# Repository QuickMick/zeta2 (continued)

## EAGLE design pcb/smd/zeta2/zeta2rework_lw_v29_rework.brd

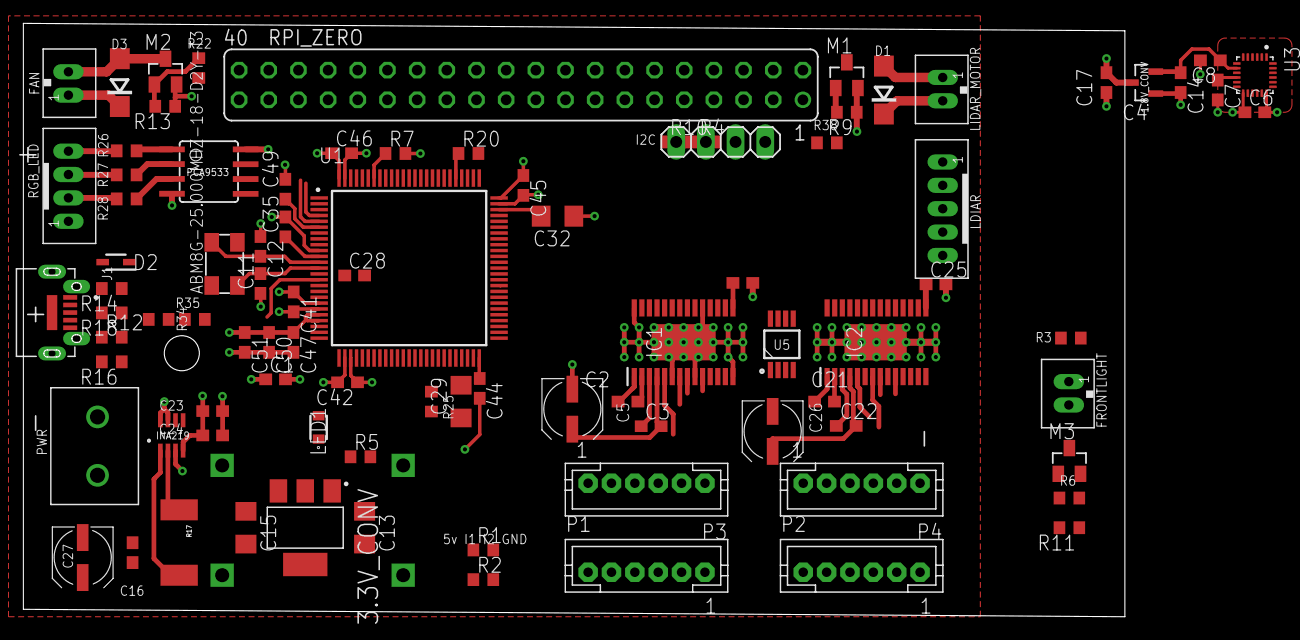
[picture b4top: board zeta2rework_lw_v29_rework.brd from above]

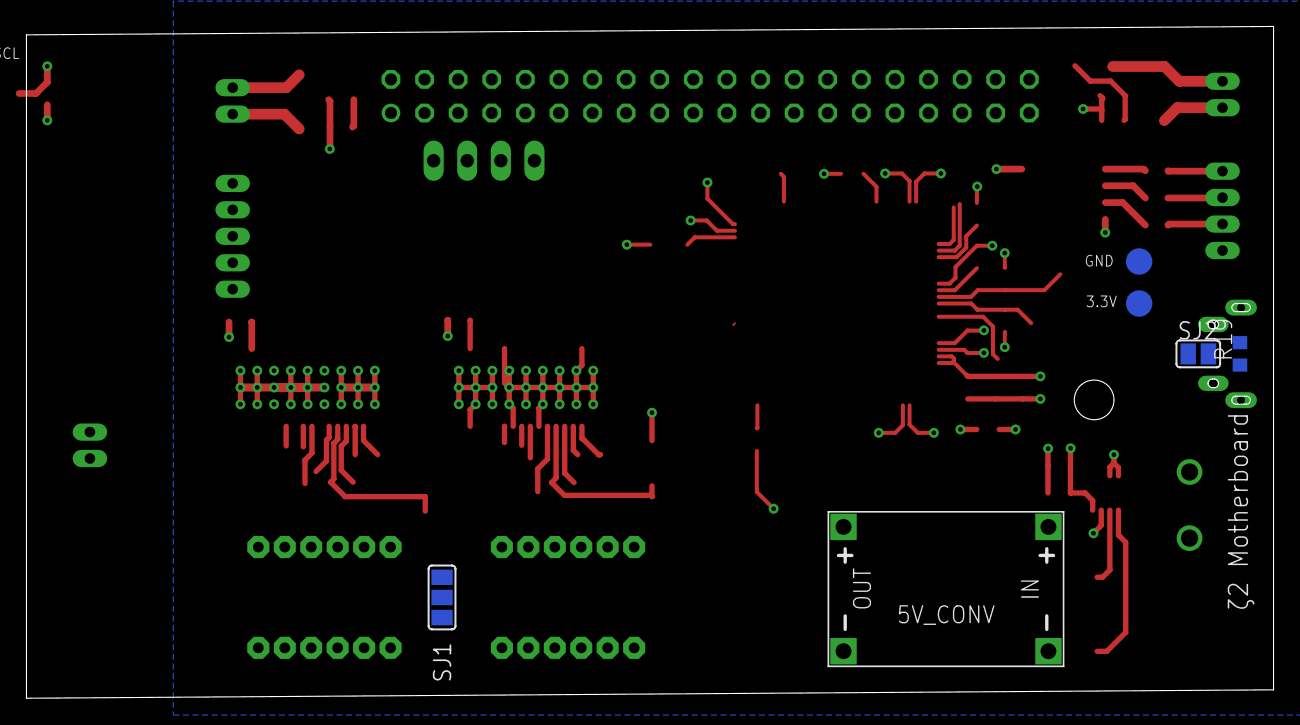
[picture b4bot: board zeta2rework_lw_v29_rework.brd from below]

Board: 4 copper layers, 94.3 x 50.8 mm, 96 parts (6 on the bottom side), 91 nets.

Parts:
1.8V_CONV: MCP1700T-1802E/TT; SOT95P237X112-3N
3.3V: TPSQTP20R; TP20R
3.3V_CONV: NCP1117LPST33T3G; SOT230P700X175-4N
5V_CONV: DC-DC-STEP-DOWN-MP2307
ABM8G-25.000MHZ-18-D2Y-T3: 25mhz; 5.0X3.2_KX-9A
C1: 4.7µf; C0603
C2, C21: 0.01µf 100v; C0603
C3, C22: 0.1µF 16v; C0603
C4, C25: 0.47µF 6.3v; C0603
C5, C26: 47µF; UD-5X5,8_NICHICON
C6, C7, C8: 0.1nF; C0603
C11, C12: Xpf; C0603
C13, C15: 10µF; C1206
C14, C17: 1µF; C0603
C16, C24: 0.1µF; C0603
C23: 100nf; C0603
C27: 100µF; UD-5X5,8_NICHICON
C28, C35, C41, C42, C44, C45, C46, C47, C49, C50: 100nF; C0603
C29, C32: 2.2µf Low ESR < 2ohm; C1206
C51: 1µf; C0603
D1, D3: 1N4004 SMD; DO214AC
D2: BAT60JFILM; SOD2513X117N
FAN: JST-PH_2-PIN_HEADER; JST_B2B-PH_HEADER
FRONTLIGHT: JST-PH_2-PIN_HEADER; JST_B2B-PH_HEADER
GND: TPSQTP20R; TP20R
I2C: 1X04
IC1, IC2: DRV8844PWPR; SOP65P640X120-29N
INA219: INA219; SOT23-8
J1: UJ2-MIBH2-4-SMT-TR; CUI_UJ2-MIBH2-4-SMT-TR
LDIAR: JST-PH_5-PIN_HEADER; JST_B5B-PH_HEADER
LED1: LT M673; LTM673-N1R2-25
LIDAR_MOTOR: JST-PH_2-PIN_HEADER; JST_B2B-PH_HEADER
M1, M2, M3: IRLML2502; SOT23
P1, P2, P3, P4: JST-PH6
PCA9533: PCA9533; SOIC8
PWR: 691137710002
R1, R2, R4, R7, R10: 10k; R0603
R3: 0R; R0603
R5, R26, R27, R28: 220R; R0603
R6, R22, R38: 22R; R0603
R9, R11, R13, R16, R20, R34: 100k; R0603
R12: 1k5; R0603
R14, R18: 22r; R0603
R17: 0.1/1% (PT2512FK-070R1L); 2512
R19: 100r; R0603
R25: 4k7; R0603
R35: 69k; R0603
RGB_LED: JST-PH_4-PIN_HEADER; JST_B4B-PH_HEADER
RPI_ZERO: FE20-2
SJ1: SJ_2
SJ2: SJ
U1: STM32F427VI; QFP50P1600X1600X160-100N
U3: ICM-20948; QFN40P300X300X105-25N
U5: DS18B20U+; SOP65P490X95-8N

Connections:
+1.8V: 1.8V_CONV.2, C8.1, C14.1, U3.8
+3V3: 1.8V_CONV.3, 3.3V.TP, 3.3V_CONV.2, 3.3V_CONV.4, C1.1, C6.1, C13.1, C17.1, C23.1, C24.1, C35.1, C41.1, C42.1, C44.1, C45.1, C46.1, C47.1, C49.1, C50.1, C51.1, IC1.16, IC2.16, INA219.4, PCA9533.8, R1.1, R2.1, R4.1, R10.1, R12.2, R20.2, R25.2, SJ1.3, U1.6, U1.11, U1.19, U1.21, U1.22, U1.28, U1.50, U1.75, U1.100, U3.13, U5.8
+5V: 3.3V_CONV.3, 5V_CONV.OUT+, C15.1, D2.1, I2C.4, LDIAR.P5, R3.1, R5.2, RGB_LED.P1, RPI_ZERO.38, RPI_ZERO.40, SJ1.1
+8V: 5V_CONV.IN+, C3.2, C5.+, C22.2, C26.+, D1.C, D3.C, FAN.P1, IC1.4, IC1.11, IC2.4, IC2.11, INA219.2, LIDAR_MOTOR.P2, R17.1
BAT_LVL: R34.1, R35.2, U1.15
DEC_LB_1: P1.3, U1.31
DEC_LB_2: P1.4, U1.32
DEC_LF_1: P3.3, U1.23
DEC_LF_2: P3.4, U1.24
DEC_RB_1: P2.3, U1.63
DEC_RB_2: P2.4, U1.64
DEC_RF_1: P4.3, U1.59
DEC_RF_2: P4.4, U1.60
GND: 1.8V_CONV.1, 3.3V_CONV.1, 5V_CONV.IN-, 5V_CONV.OUT-, C1.2, C4.2, C5.-, C6.2, C7.2, C8.2, C11.1, C12.1, C13.2, C14.2, C15.2, C16.2, C17.2, C23.2, C24.2, C25.2, C26.-, C27.-, C28.2, C29.1, C32.1, C35.2, C41.2, C42.2, C44.2, C45.2, C46.2, C47.2, C49.2, C50.2, C51.2, GND.TP, I2C.3, IC1.6, IC1.9, IC1.14, IC1.19, IC1.28, IC1.29, IC2.6, IC2.9, IC2.14, IC2.19, IC2.28, IC2.29, INA219.3, INA219.7, INA219.8, J1.5, LDIAR.P4, LED1.1, M1.2, M2.2, M3.2, P1.5, P2.5, P3.5, P4.5, PCA9533.4, PWR.2, R7.2, R9.1, R11.1, R13.1, R35.1, RPI_ZERO.1, RPI_ZERO.8, RPI_ZERO.12, RPI_ZERO.15, RPI_ZERO.22, RPI_ZERO.28, RPI_ZERO.31, RPI_ZERO.36, SJ2.1, U1.10, U1.20, U1.27, U1.74, U1.99, U3.18, U5.4
I2C1_SCL: INA219.5, PCA9533.6, R1.2, U1.92, U3.23
I2C1_SDA: INA219.6, PCA9533.7, R2.2, U1.93, U3.24
I2C3_SCL: I2C.1, R4.2, U1.67
I2C3_SDA: I2C.2, R10.2, U1.66
LIDAR_POS_INT: LDIAR.P3, U1.81
M_LB_IN1: IC1.23, U1.84
M_LB_IN2: IC1.21, U1.85
M_LF_IN1: IC1.27, U1.82
M_LF_IN2: IC1.25, U1.83
M_PWM_LB: IC1.20, IC1.22, U1.45
M_PWM_LF: IC1.24, IC1.26, U1.44
M_PWM_RB: IC2.20, IC2.22, U1.5
M_PWM_RF: IC2.24, IC2.26, U1.4
M_RB_IN1: IC2.23, U1.88
M_RB_IN2: IC2.21, U1.89
M_RF_IN1: IC2.27, U1.86
M_RF_IN2: IC2.25, U1.87
M_SLEEP: IC1.17, IC2.17, U1.90
unnamed: C21.2, IC2.2
unnamed: C21.1, IC2.1
unnamed: C22.1, IC2.3
unnamed: IC2.10, P2.1
unnamed: J1.3, R12.1, R18.2
unnamed: FRONTLIGHT.P1, R3.2
unnamed: LED1.2, R5.1
unnamed: C7.1, U3.10
unnamed: FRONTLIGHT.P2, M3.3
unnamed: M3.1, R6.2, R11.2
unnamed: IC2.5, P4.1
unnamed: IC2.7, P4.6
unnamed: ABM8G-25.000MHZ-18-D2Y-T3.1, C11.2, U1.13
unnamed: IC1.5, P3.1
unnamed: D2.2, J1.1
unnamed: R7.1, U1.94
unnamed: J1.4, R16.2
unnamed: C2.2, IC1.2
unnamed: IC2.8, P2.6
unnamed: C2.1, IC1.1
unnamed: C3.1, IC1.3
unnamed: PCA9533.1, R26.1
unnamed: PCA9533.2, R27.1
unnamed: PCA9533.3, R28.1
unnamed: R19.1, SJ2.2
unnamed: C25.1, IC2.15
unnamed: IC1.7, P3.6
unnamed: IC1.8, P1.6
unnamed: C4.1, IC1.15
unnamed: IC1.10, P1.1
unnamed: R26.2, RGB_LED.P4
unnamed: P1.2, P2.2, P3.2, P4.2, SJ1.2
unnamed: R27.2, RGB_LED.P3
unnamed: J1.2, R14.2
unnamed: R28.2, RGB_LED.P2
unnamed: C29.2, U1.49
unnamed: M2.1, R13.2, R22.2
unnamed: M1.1, R9.2, R38.2
unnamed: D1.A, LIDAR_MOTOR.P1, M1.3
unnamed: J1.SH1, J1.SH2, J1.SH3, J1.SH4, J1.SH5, R19.2
unnamed: ABM8G-25.000MHZ-18-D2Y-T3.3, C12.2, U1.12
unnamed: C32.2, U1.73
unnamed: D3.A, FAN.P2, M2.3
NFAULT: IC1.18, IC2.18, R20.1, U1.80
NRST: C28.1, RPI_ZERO.26, U1.14
PWM_FAN: R22.1, U1.96
PWM_LIDAR: R38.1, U1.95
PWM_LIGHT: R6.1, U1.40
SWCLK: RPI_ZERO.20, U1.76
SWDIO: RPI_ZERO.24, U1.72
TEMPERATURE: R25.1, U1.42, U5.1
UART3_RX: LDIAR.P1, U1.56
UART3_TX: LDIAR.P2, U1.55
UART4_RX: RPI_ZERO.34, U1.79
UART4_TX: RPI_ZERO.32, U1.78
USB_OTG_DM: R14.1, U1.70
USB_OTG_DP: R18.1, U1.71
USB_OTG_ID: R16.1, U1.69
V+: C16.1, C27.+, INA219.1, PWR.1, R17.2, R34.2
